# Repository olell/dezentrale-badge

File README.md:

# Dezentrale Blinky Logo

## Update Firmware

You can flash the latest Firmware directly using your web browser using [CH32WebFlash](https://olell.github.io/CH32WebFlashTool/?image=https://github.com/olell/dezentrale-badge/releases/download/v0.1.0/main.bin)

## Photos

## License

- Firmware source code is release under MIT License (C) 2025 Ole Lange
- The hardware is licensed under CC BY-NC-SA 4.0

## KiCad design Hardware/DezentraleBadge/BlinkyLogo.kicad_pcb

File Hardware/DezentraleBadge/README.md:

# Dezentrale Badge Hardware Version 1

This folder contains the KiCad project for the BlinkyLogo V1

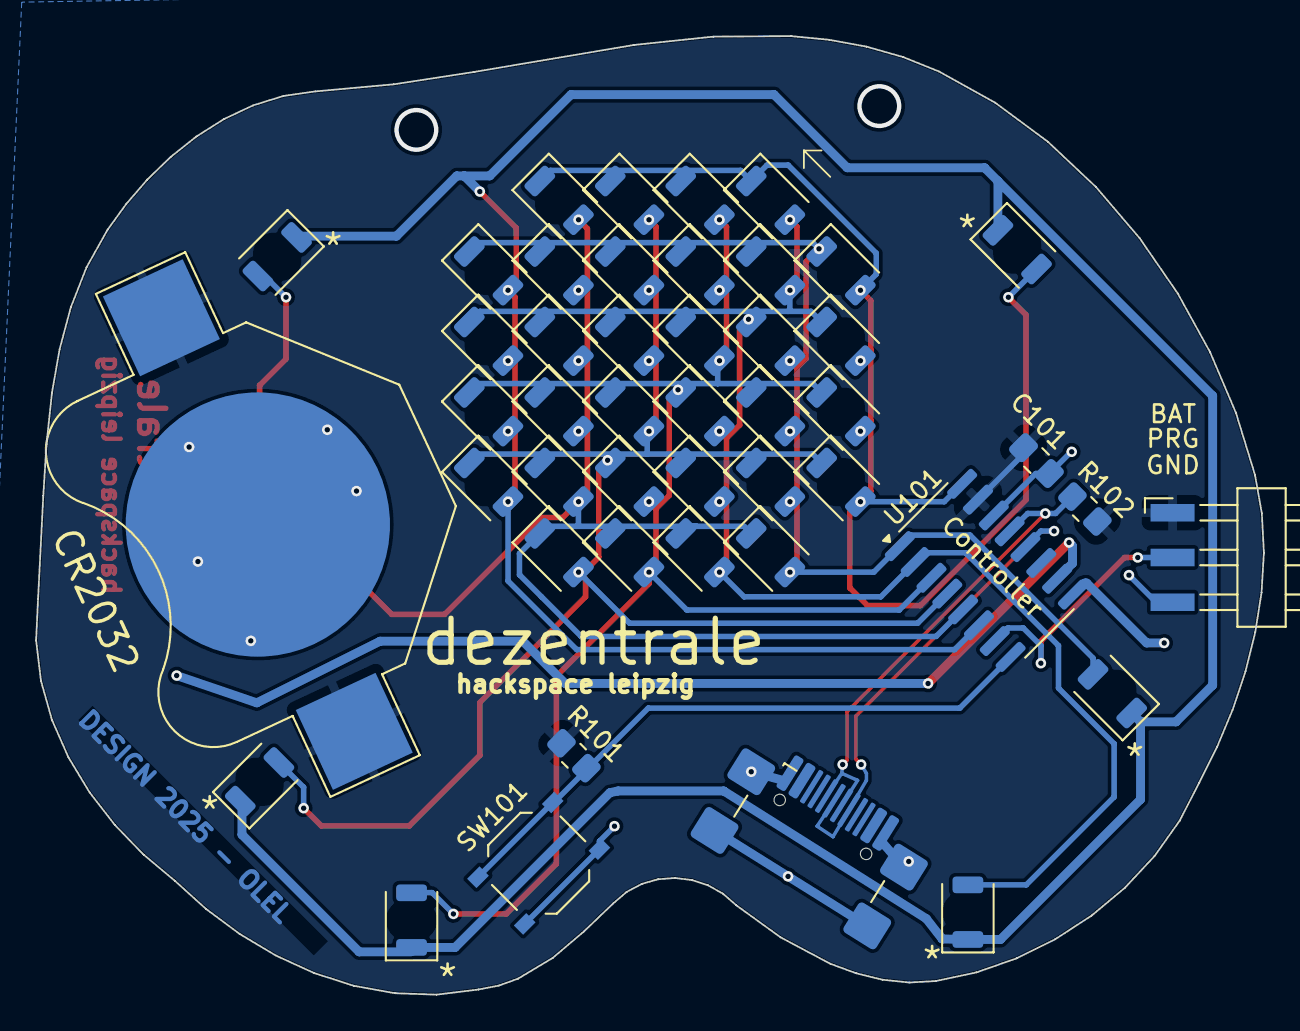
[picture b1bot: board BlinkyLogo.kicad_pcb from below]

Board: 2 copper layers, 69.7 x 54.4 mm, 46 parts (46 on the bottom side), 13 nets.

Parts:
BT101: CR2032; BatteryHolder_Multicomp_BC-2001_1x2032
C101: 100nF; C_0805_2012Metric_Pad1.18x1.45mm_HandSolder
D102, D103, D104, D105, D107, D108, D109, D110, D111, D112, D113, D114, D115, D116, D117, D118, D119, D120, D121, D122, D123, D124, D125, D126, D127, D128, D129, D130, D132, D133, D134, D135, D137, D138, D139, D140, D141, D142: LED_45deg; LED_1206_3216Metric_ReverseMount_Hole1.8x2.4mm
J101: PROG; Harwin_M20-89003xx_1x03_P2.54mm_Horizontal
J102: USB_C_Receptacle_USB2.0_16P; USB_C_Receptacle_GCT_USB4110
R101: 10kΩ; R_0805_2012Metric_Pad1.20x1.40mm_HandSolder
R102: 1.5kΩ; R_0805_2012Metric_Pad1.20x1.40mm_HandSolder
SW101: Button; SW_Push_1P1T_XKB_TS-1187A
U101: CH32V003AxMx; SOP-16_3.9x9.9mm_P1.27mm

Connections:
+BATT: BT101.1 (+), C101.2, J101.1, R101.2, R102.1, U101.15 (VDD)
/BUTTON: R101.1, SW101.1, U101.8 (PD4)
/LED0: D102.1 (K), D103.1 (K), D104.1 (K), D105.1 (K), D107.2 (A), D113.2 (A), D119.2 (A), D125.2 (A), D137.2 (A), U101.16 (PC0)
/LED1: D107.1 (K), D108.1 (K), D109.1 (K), D110.1 (K), D111.1 (K), D112.1 (K), D114.2 (A), D120.2 (A), D126.2 (A), D132.2 (A), D138.2 (A), U101.1 (PC1)
/LED2: D102.2 (A), D108.2 (A), D113.1 (K), D114.1 (K), D115.1 (K), D116.1 (K), D117.1 (K), D118.1 (K), D121.2 (A), D127.2 (A), D133.2 (A), D139.2 (A), U101.2 (PC2)
/LED3: D103.2 (A), D109.2 (A), D115.2 (A), D119.1 (K), D120.1 (K), D121.1 (K), D122.1 (K), D123.1 (K), D124.1 (K), D128.2 (A), D134.2 (A), D140.2 (A), U101.3 (PC3)
/LED4: D104.2 (A), D110.2 (A), D116.2 (A), D122.2 (A), D125.1 (K), D126.1 (K), D127.1 (K), D128.1 (K), D129.1 (K), D130.1 (K), D135.2 (A), D141.2 (A), U101.4 (PC4)
/LED5: D105.2 (A), D111.2 (A), D117.2 (A), D123.2 (A), D129.2 (A), D132.1 (K), D133.1 (K), D134.1 (K), D135.1 (K), D142.2 (A), U101.5 (PC6)
/LED6: D112.2 (A), D118.2 (A), D124.2 (A), D130.2 (A), D137.1 (K), D138.1 (K), D139.1 (K), D140.1 (K), D141.1 (K), D142.1 (K), U101.6 (PC7)
/SWIO: J101.2, U101.7 (PD1)
/USB_DN: J102.A7 (D-), J102.B7 (D-), R102.2, U101.13 (PA2)
/USB_DP: J102.A6 (D+), J102.B6 (D+), U101.12 (PA1)
GND: BT101.2 (-), C101.1, J101.3, J102.A1 (GND), J102.A12 (GND), J102.B1 (GND), J102.B12 (GND), J102.S1 (SHIELD), SW101.2, U101.14 (VSS)

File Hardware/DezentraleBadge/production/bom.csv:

Designator,Footprint,Quantity,Value,LCSC Part #
BT101,BatteryHolder_Multicomp_BC-2001_1x2032,1,CR2032,C6937139
C101,0805,1,100nF,C28233
"D102, D103, D104, D105, D107, D108, D109, D110, D111, D112, D113, D114, D115, D116, D117, D118, D119, D120, D121, D122, D123, D124, D125, D126, D127, D128, D129, D130, D132, D133, D134, D135, D137, D138, D139, D140, D141, D142",1206,38,LED_45deg,C3646940
J101,Harwin_M20-89003xx_1x03_P2.54mm_Horizontal,1,PROG,
J102,USB_C_Receptacle_GCT_USB4110,1,USB_C_Receptacle_USB2.0_16P,
R101,0805,1,10kΩ,C17414
R102,0805,1,1.5kΩ,C17414
SW101,SW_Push_1P1T_XKB_TS-1187A,1,Button,C318884
U101,SOP-16_3.9x9.9mm_P1.27mm,1,CH32V003AxMx,C5346357

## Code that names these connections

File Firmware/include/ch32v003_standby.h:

// Slightly modified ch32v003_standby.h from recallmenot/ch32v003fun_wildwest
// available at: https://github.com/recallmenot/ch32v003fun_wildwest/blob/main/lib/ch32v003_standby.h
// Licensed under the MIT License.

//######## necessities

// include guards
#ifndef CH32V003_STANDBY_H
#define CH32V003_STANDBY_H

// includes
#include<stdint.h>								//uintN_t support
#include"ch32fun.h"



/*######## library description

This library makes sending the CH32V003 to sleep easy.
You can use the auto-wakeup timer, a pin or both, to exit standby and resume operation.

Expect around 10uA total power consumption in standby.
The LSI oscillator used for auto-wakeup uses 0.6uA.

*/



/*######## library usage and configuration

## auto-wakeup timer

The auto-wakeup timer takes two arguments to set the delay:
a clock prescaler divider and a count which, when reached, triggers the auto-wakeup event.

The autowakeup delay can be calculated by:

t = AWUWR / (fLSI / AWUPSC)

Where AWUWR (the count) can be 1 to 63, fLSI is always 128000 and AWUPSC (the prescaler divider), for practical purposes is 2048, 4096, 10240 or 61440, though lower values are possible.
The maximum auto-wakeup delay is 30s.

## wake by GPIO pins

When using GPIO pins to wake, there is a limitation on which can be set to this task simultaneously.
A pin can only be connected to its preassigned event channel:
PA1, PC1 and PD1 can only be connected to event channel 1, so you will have to pick one of the three.
Likewise, one of PA2, PC2 and PD2 can be connected to event channel 2, etc.

*/



/*######## features: use your desired before #including this library!

to have standby_enter() automatically restore the HSI speed to 48MHz after standby (else it will be 24MHz)
#define STANDBY_RESTORE_HSI_48MHz
*/



//######## references: use these

// port definitions for the standby_gpio_assign functions
#define STANDBY_GPIO_PORT_A 0b00
#define STANDBY_GPIO_PORT_C 0b10
#define STANDBY_GPIO_PORT_D 0b11

// port definitions for the standby_gpio_assign_pin functions
#define STANDBY_TRIGGER_DIRECTION_RISING	0b01
#define STANDBY_TRIGGER_DIRECTION_FALLING	0b10
#define STANDBY_TRIGGER_DIRECTION_BOTH		0b11



//######## function overview (declarations): use these!

// initialize standby with auto-wakeup timer
static inline void standby_autowakeup_init(const uint8_t window_count, const uint8_t PWR_AWU_Prescaler);

// initialize standby with GPIO wakeup
static inline void standby_gpio_init();

// configure GPIO pin for wakeup
static inline void standby_gpio_assign_pin(uint8_t standby_gpio_port, uint8_t pin_number, uint8_t standby_trigger_direction);
// configure GPIO pin with pull-up for wakeup
static inline void standby_gpio_assign_button(GPIO_TypeDef* gpio_port, uint8_t pin_number);

// enter standby mode
static inline void standby_enter();



//######## internal function declarations



//######## internal variables



//######## preprocessor macros



//######## preprocessor #define requirements


//######## small function definitions, static inline



static inline void standby_autowakeup_init(const uint8_t window_count, const uint8_t PWR_AWU_Prescaler) {
	// enable power interface module clock
	RCC->APB1PCENR |= RCC_APB1Periph_PWR;

	// enable low speed oscillator (LSI)
	RCC->RSTSCKR |= RCC_LSION;
	while ((RCC->RSTSCKR & RCC_LSIRDY) == 0) {}

	// enable AutoWakeUp event
	EXTI->EVENR |= EXTI_Line9;
	EXTI->FTENR |= EXTI_Line9;

	// configure AWU prescaler
	PWR->AWUPSC |= PWR_AWU_Prescaler;

	// configure AWU window comparison value
	PWR->AWUWR &= ~0x3f;
	PWR->AWUWR |= window_count;

	// enable AWU
	PWR->AWUCSR |= (1 << 1);

	// select standby on power-down
	PWR->CTLR |= PWR_CTLR_PDDS;

	// peripheral interrupt controller send to deep sleep
	PFIC->SCTLR |= (1 << 2);
}



static inline void standby_gpio_init() {
	// enable alternate IO function module clock
	RCC->APB2PCENR |= RCC_AFIOEN;

	// select standby on power-down
	PWR->CTLR |= PWR_CTLR_PDDS;

	// peripheral interrupt controller send to deep sleep
	PFIC->SCTLR |= (1 << 2);
}



static inline void standby_gpio_assign_pin(uint8_t standby_gpio_port, uint8_t pin_number, uint8_t standby_trigger_direction) {
	// enable the correct GPIO port register
	RCC->APB2PCENR |= (1 << (2 + standby_gpio_port));

	// assign pin 2 interrupt from portD (0b11) to EXTI channel 2
	AFIO->EXTICR |= (uint32_t)(standby_gpio_port << (pin_number * 2));

	// enable line2 interrupt event
	EXTI->EVENR |= (1 << pin_number);

	// set trigger condition
	EXTI->RTENR |= (standby_trigger_direction & 0b01) * (1 << pin_number);
	EXTI->FTENR |= (standby_trigger_direction >> 1) * (1 << pin_number);
}



static inline void standby_gpio_assign_button(GPIO_TypeDef* gpio_port, uint8_t pin_number) {
	// configure button as input, pullup
	gpio_port->CFGLR &= ~(0xf << (pin_number * 4));
	gpio_port->CFGLR |= (GPIO_CNF_IN_PUPD) << (pin_number * 4);
	gpio_port->BSHR = (1 << pin_number);
}



static inline void standby_enter() {
	__WFE();
	// after standby, core clock will be 24MHz HSI
	#ifdef STANDBY_RESTORE_HSI_48MHz
	// restore clock to full speed
	SystemInit48HSI();
    #else
    SystemInit();
	#endif
}



//######## small internal function definitions, static inline



//######## implementation block
//#define CH32V003_LIBRARYNAME_IMPLEMENTATION //enable so LSP can give you text colors while working on the implementation block, disable for normal use of the library
#if defined(CH32V003_LIBRARYNAME_IMPLEMENTATION)



#endif // CH32V003_LIBRARYNAME_IMPLEMENTATION
#endif // CH32V003_LIBRARYNAME_H

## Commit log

2025-05-02 Added KiCad project
2025-05-02 Added schematic/pcb pdf files
2025-05-02 Added Firmware code
2025-05-02 Added photos
2025-05-02 Optimized matrix control + added pulse
2025-05-02 Enabled PLL
2025-05-02 Added more brightness levels
2025-05-02 Added rolling text animation
2025-05-02 Changed font
2025-05-02 Changed text
2025-05-02 Added face animation
2025-05-04 Optimized matrix driver by precalculating register values
2025-05-04 Added compiler flag to optimize towards speed
2025-05-04 impl button interrupt
2025-05-04 Fixed overflowing timer
2025-05-05 Disabling external interrupt while sleep
2025-05-08 updated animations
2025-05-18 Implemented capacitive touch buttons
2025-05-18 Added doc about usb bootloader
2025-05-18 Simplified bootloader workflow
2025-05-18 Bump HW rev 2
2025-05-27 kicad
2025-05-27 Changed flash cmd to usb
2025-05-27 Added ch32fun submodule
2025-05-27 Added instruction to get submodule
2025-05-27 Added gh workflow
2025-05-27 Added release workflow
2025-05-27 updated release workflow
2025-05-27 Disabled initramfs/man-db update
2025-05-27 Added license notice to README
2025-05-27 Extended gitignore
2025-05-27 created assets
2025-05-28 moved matrixDisplay to ram
2025-05-28 moved systick handler to ram
2025-05-28 using 1 dimensional pixel addressing
2025-05-28 changed MAX_BRIGHTNESS to 15
2025-06-01 inlined matrix function
2025-06-01 added register attribute to variables
2025-06-02 Updated ch32fun
2025-06-02 cleaned up comments
2025-06-02 Added flag to only enable touch if required
2025-06-02 Added touch flag to fade animation
2025-06-02 use both touch channels in fade
2025-06-19 ⚡️ changed to fixed point arithmetic

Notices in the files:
Hardware/DezentraleBadge/BlinkyLogo.kicad_pcb:
CC-BY-SA
